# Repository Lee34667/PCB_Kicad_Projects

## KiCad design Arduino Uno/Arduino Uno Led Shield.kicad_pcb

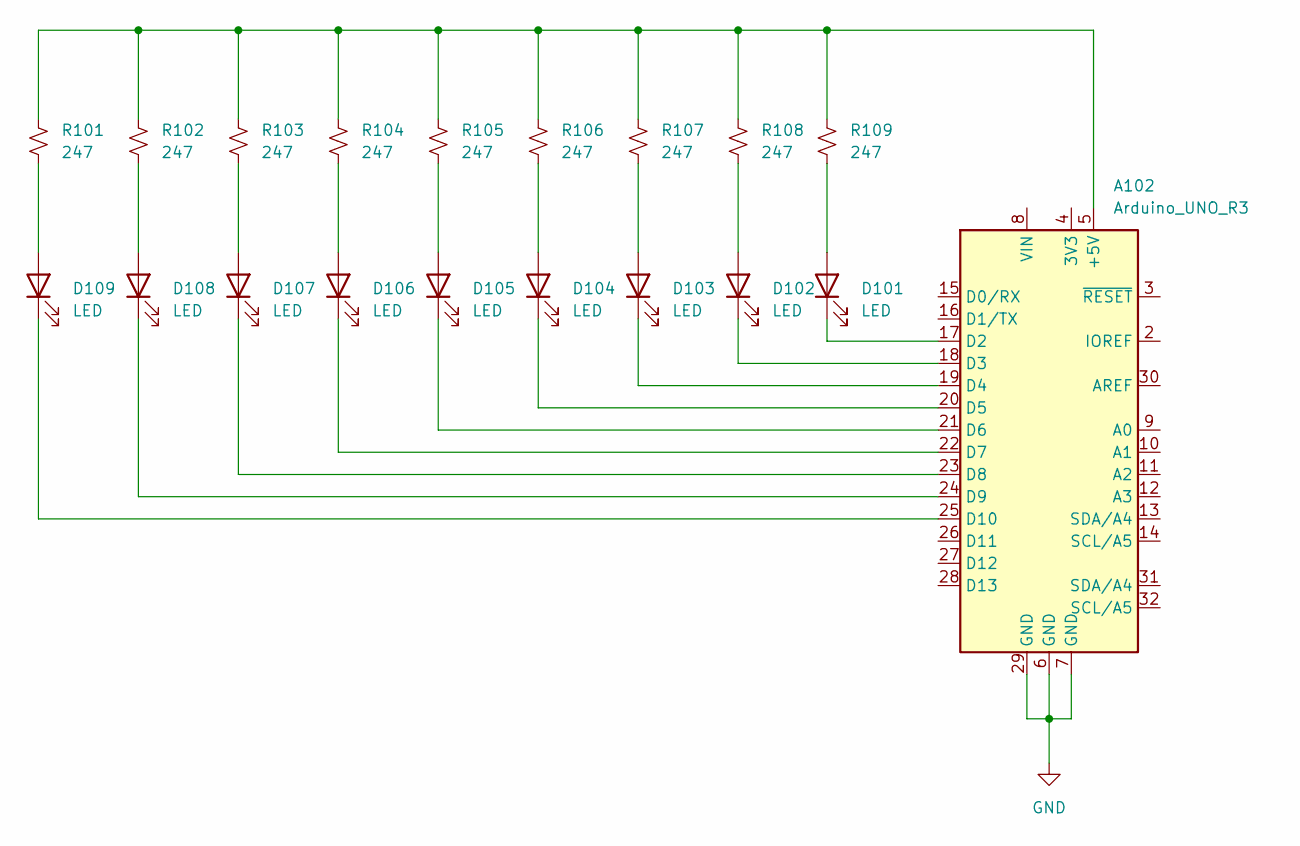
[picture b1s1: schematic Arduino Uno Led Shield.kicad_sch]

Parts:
A102: Arduino_UNO_R3
D101, D102, D103, D104, D105, D106, D107, D108, D109: LED; LED_0805_2012Metric
R101, R102, R103, R104, R105, R106, R107, R108, R109: 247; R_0603_1608Metric

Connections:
unnamed 1: A102.5 (+5V), R101.1, R102.1, R103.1, R104.1, R105.1, R106.1, R107.1, R108.1, R109.1; also elsewhere on the board
unnamed 2: A102.17 (D2), D101.1 (K); also elsewhere on the board
unnamed 3: A102.18 (D3), D102.1 (K); also elsewhere on the board
unnamed 4: A102.19 (D4), D103.1 (K); also elsewhere on the board
unnamed 5: A102.20 (D5), D104.1 (K); also elsewhere on the board
unnamed 6: A102.21 (D6), D105.1 (K); also elsewhere on the board
unnamed 7: A102.22 (D7), D106.1 (K); also elsewhere on the board
unnamed 8: A102.23 (D8), D107.1 (K); also elsewhere on the board
unnamed 9: A102.24 (D9), D108.1 (K); also elsewhere on the board
unnamed 10: A102.25 (D10), D109.1 (K); also elsewhere on the board
unnamed: A102.6 (GND), A102.7 (GND), A102.29 (GND)
unnamed: D101.2 (A), R109.2
unnamed: D102.2 (A), R108.2
unnamed: D103.2 (A), R107.2
unnamed: D104.2 (A), R106.2
unnamed: D105.2 (A), R105.2
unnamed: D106.2 (A), R104.2
unnamed: D107.2 (A), R103.2
unnamed: D108.2 (A), R102.2
unnamed: D109.2 (A), R101.2

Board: 2 copper layers, 19 parts (0 on the bottom side), 20 nets, no tracks yet.

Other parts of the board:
A101: Arduino_UNO_R2

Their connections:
GND: A101.6 (GND), A101.7 (GND), A101.29 (GND)
unnamed 1: A101.5 (+5V); also elsewhere on the board
unnamed 2: A101.17 (D2); also elsewhere on the board
unnamed 3: A101.18 (D3); also elsewhere on the board
unnamed 4: A101.19 (D4); also elsewhere on the board
unnamed 5: A101.20 (D5); also elsewhere on the board
unnamed 6: A101.21 (D6); also elsewhere on the board
unnamed 7: A101.22 (D7); also elsewhere on the board
unnamed 8: A101.23 (D8); also elsewhere on the board
unnamed 9: A101.24 (D9); also elsewhere on the board
unnamed 10: A101.25 (D10); also elsewhere on the board

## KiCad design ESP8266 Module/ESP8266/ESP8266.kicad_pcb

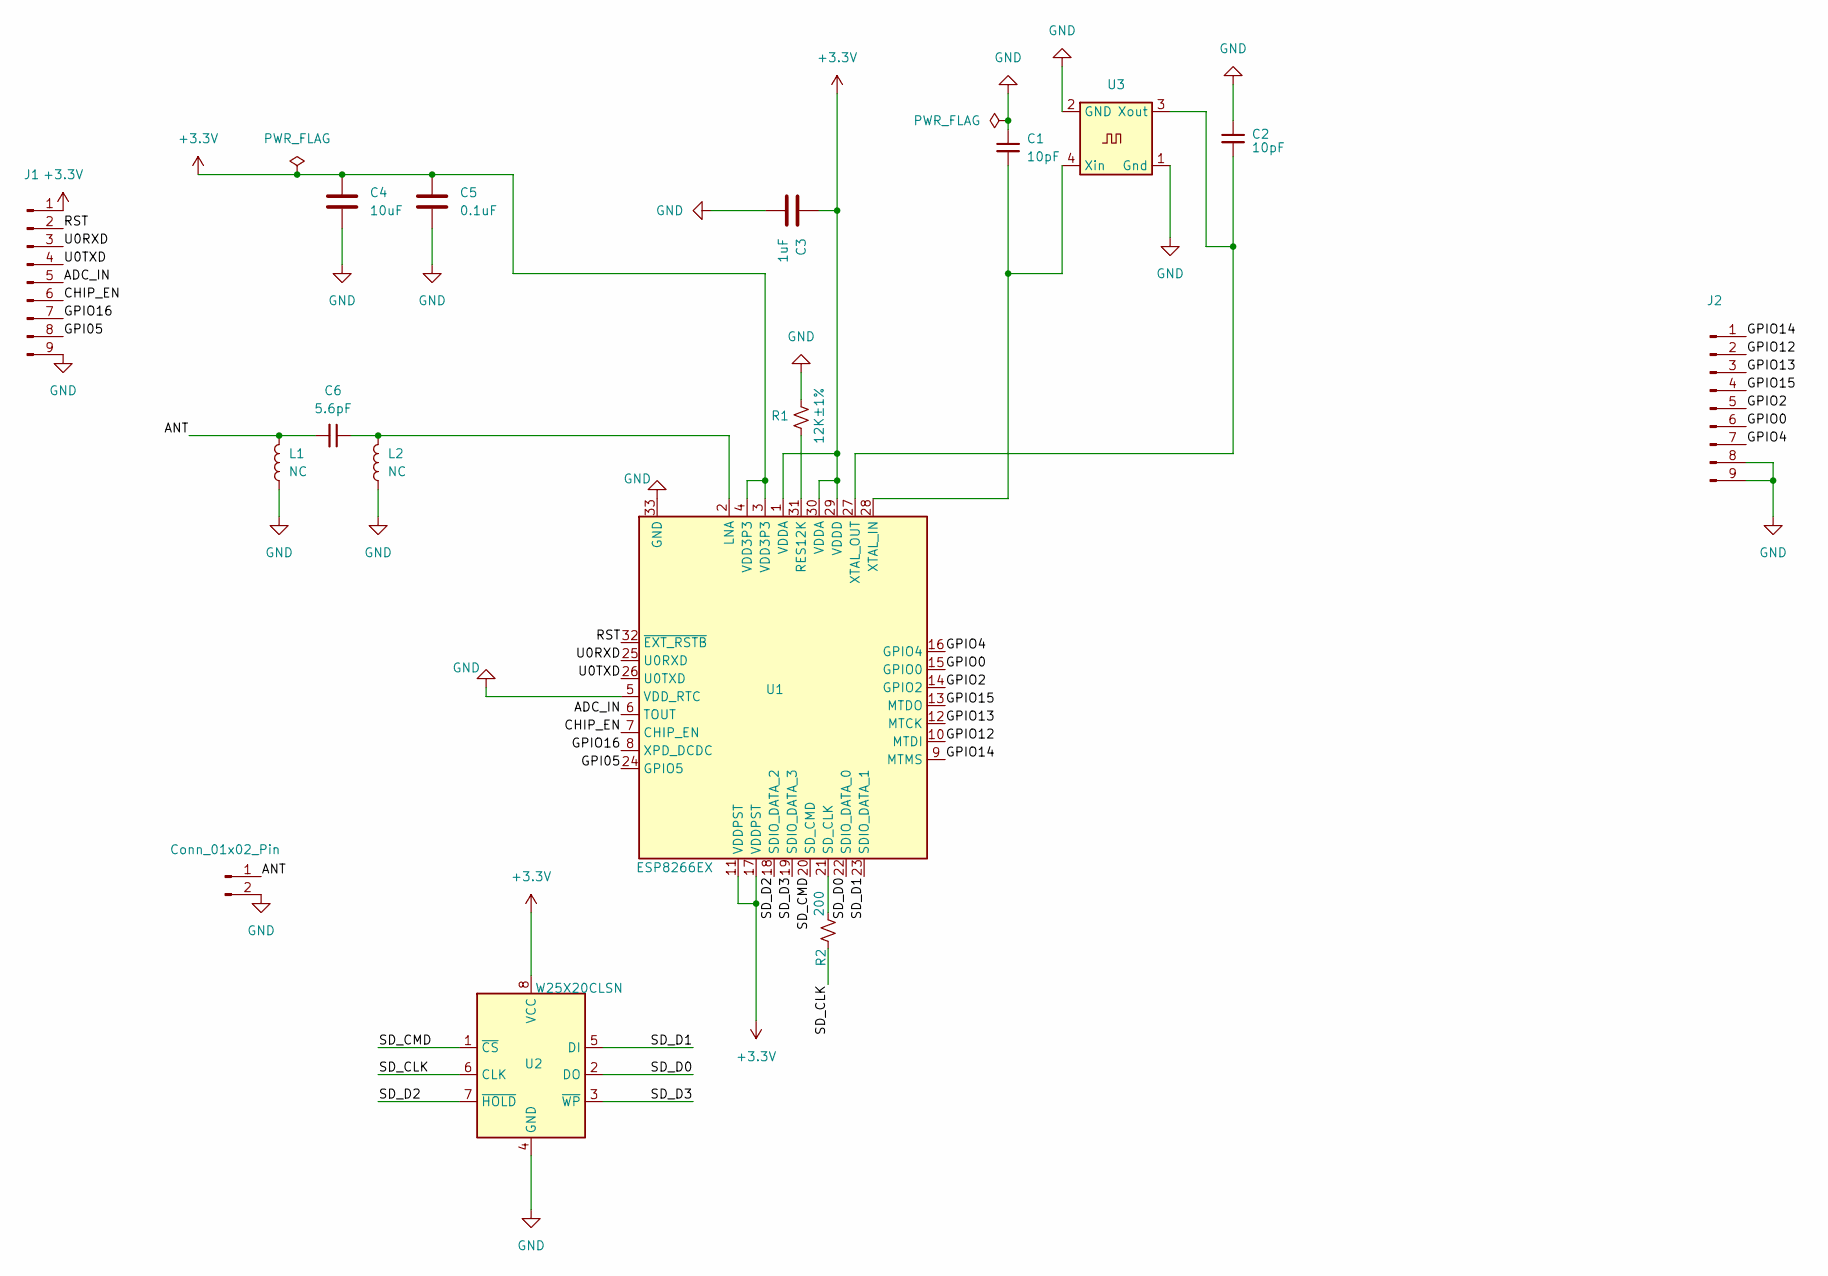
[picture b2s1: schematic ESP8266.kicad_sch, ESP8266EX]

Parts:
C1, C2: 10pF; C_0603_1608Metric_Pad1.08x0.95mm_HandSolder
C3: 1uF; C_0603_1608Metric_Pad1.08x0.95mm_HandSolder
C4: 10uF; C_0603_1608Metric_Pad1.08x0.95mm_HandSolder
C5: 0.1uF; C_0603_1608Metric_Pad1.08x0.95mm_HandSolder
C6: 5.6pF; C_0603_1608Metric_Pad1.08x0.95mm_HandSolder
J1: Conn_01x09_Pin; PinHeader_1x09_P2.54mm_Vertical
J2: PinHeader_1x09_P2.54mm_Vertical
J3: Conn_01x02_Pin; PinHeader_1x02_P2.54mm_Horizontal
L1, L2: NC; L_1206_3216Metric_Pad1.22x1.90mm_HandSolder
R1: 12K±1%; R_0805_2012Metric_Pad1.20x1.40mm_HandSolder
R2: 200; R_0805_2012Metric_Pad1.20x1.40mm_HandSolder
U1: ESP8266EX; QFN-32-1EP_5x5mm_P0.5mm_EP3.45x3.45mm
U2: W25X20CLSN; SOIC-8_3.9x4.9mm_P1.27mm
X1: U3; Oscillator_SMD_SeikoEpson_SG3030CM

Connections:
+3.3V: C3.1, C4.1, C5.1, J1.1, U1.1 (VDDA), U1.3 (VDD3P3), U1.4 (VDD3P3), U1.11 (VDDPST), U1.17 (VDDPST), U1.29 (VDDD), U1.30 (VDDA), U2.8 (VCC)
/ADC_IN: J1.5, U1.6 (TOUT)
/ANT: C6.2, J3.1, L1.2
/CHIP_EN: J1.6, U1.7 (CHIP_EN)
/GPI05: J1.8, U1.24 (GPIO5)
/GPIO0: J2.6, U1.15 (GPIO0)
/GPIO2: J2.5, U1.14 (GPIO2)
/GPIO4: J2.7, U1.16 (GPIO4)
/GPIO12: J2.2, U1.10 (MTDI)
/GPIO13: J2.3, U1.12 (MTCK)
/GPIO14: J2.1, U1.9 (MTMS)
/GPIO15: J2.4, U1.13 (MTDO)
/GPIO16: J1.7, U1.8 (XPD_DCDC)
/RST: J1.2, U1.32 (~EXT_RSTB)
/SD_CLK: R2.1, U2.6 (CLK)
/SD_CMD: U1.20 (SD_CMD), U2.1 (~CS)
/SD_D0: U1.22 (SDIO_DATA_0), U2.2 (DO)
/SD_D1: U1.23 (SDIO_DATA_1), U2.5 (DI)
/SD_D2: U1.18 (SDIO_DATA_2), U2.7 (~HOLD)
/SD_D3: U1.19 (SDIO_DATA_3), U2.3 (~WP)
/U0RXD: J1.3, U1.25 (U0RXD)
/U0TXD: J1.4, U1.26 (U0TXD)
GND: C1.1, C2.1, C3.2, C4.2, C5.2, J1.9, J2.8, J2.9, J3.2, L1.1, L2.1, R1.1, U1.5 (VDD_RTC), U1.33 (GND), U2.4 (GND), X1.1 (Gnd), X1.2 (GND)
unnamed: C6.1, L2.2, U1.2 (LNA)
unnamed: R1.2, U1.31 (RES12K)
unnamed: R2.2, U1.21 (SD_CLK)
unnamed: C1.2, U1.28 (XTAL_IN), X1.4 (Xin)
unnamed: C2.2, U1.27 (XTAL_OUT), X1.3 (Xout)

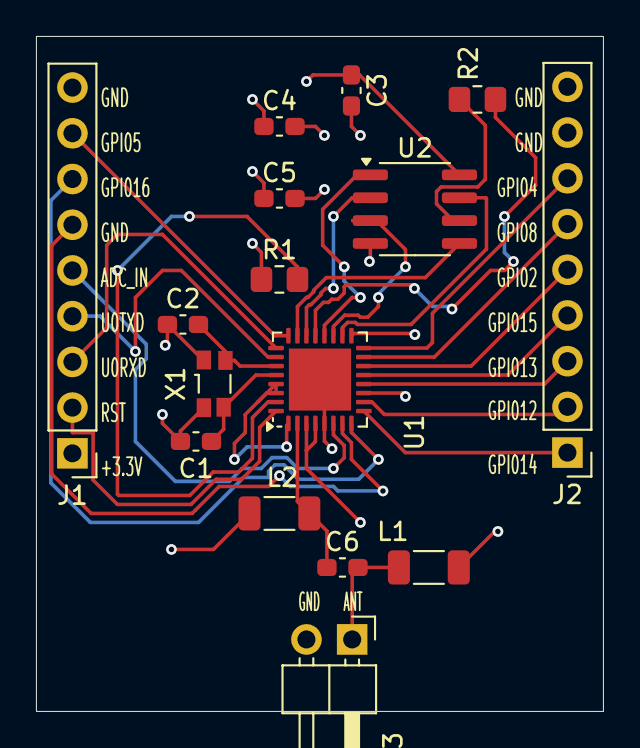
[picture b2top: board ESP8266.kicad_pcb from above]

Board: 4 copper layers, 31.5 x 37.5 mm, 16 parts (0 on the bottom side), 28 nets.

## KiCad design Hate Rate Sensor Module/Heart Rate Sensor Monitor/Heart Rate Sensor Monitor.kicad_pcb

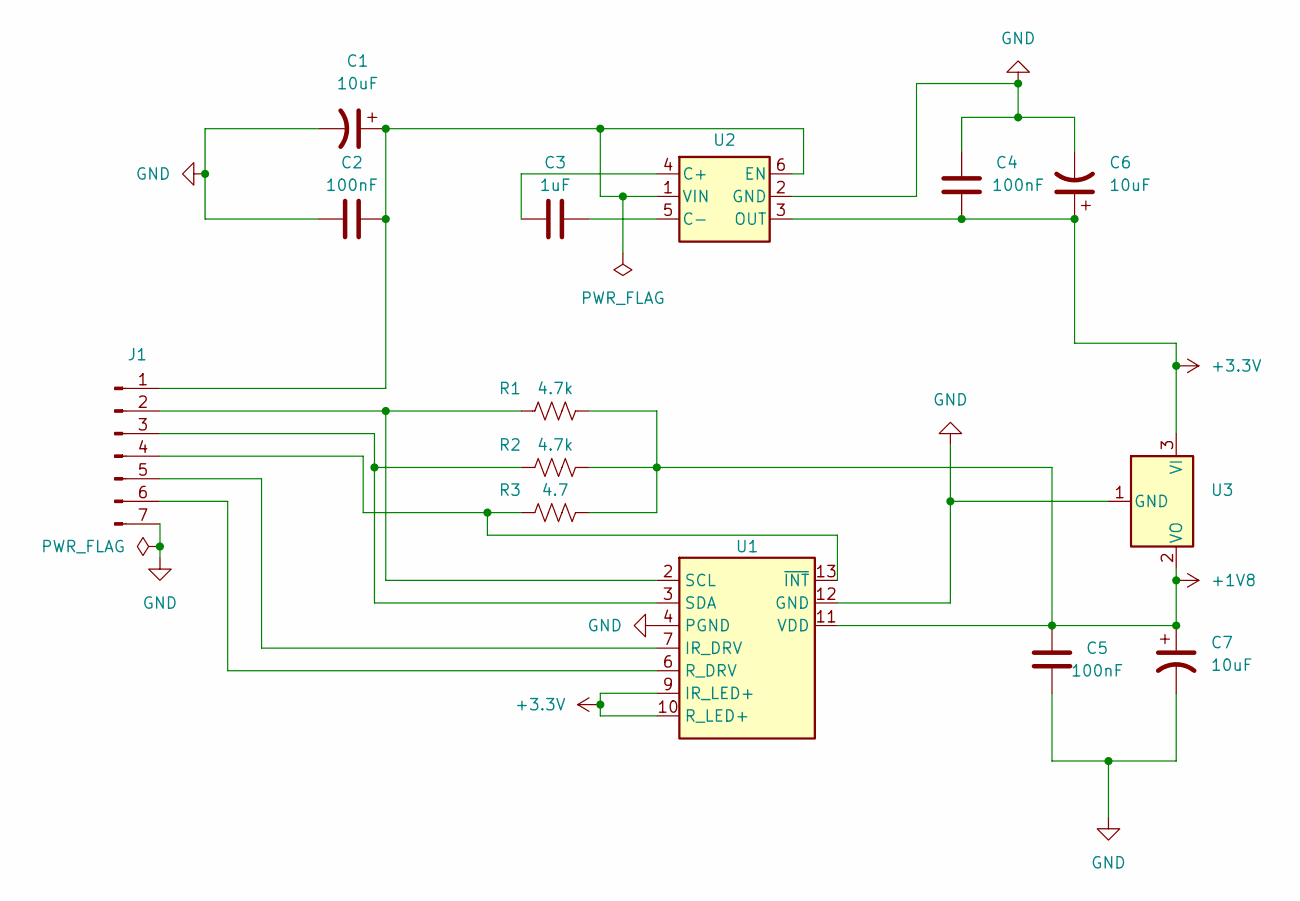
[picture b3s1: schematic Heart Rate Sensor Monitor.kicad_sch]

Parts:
C1, C6, C7: 10uF; C_0504_1310Metric_Pad0.83x1.28mm_HandSolder
C2, C4, C5: 100nF; C_0504_1310Metric_Pad0.83x1.28mm_HandSolder
C3: 1uF; C_0504_1310Metric_Pad0.83x1.28mm_HandSolder
J1: Conn_01x07_Pin; PinHeader_1x07_P1.27mm_Vertical
R1, R2: 4.7k; R_0603_1608Metric_Pad0.98x0.95mm_HandSolder
R3: 4.7; R_0603_1608Metric_Pad0.98x0.95mm_HandSolder
U1: MAX30102; Maxim_OLGA-14_3.3x5.6mm_P0.8mm
U2: TLV70028_WSON6; WSON-6_1.5x1.5mm_P0.5mm
U3: TPS7A0512PDBZ; SOT-23

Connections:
+1V8: C5.2, C7.1, R1.2, R2.2, R3.2, U1.11 (VDD), U3.2 (VO)
+3.3V: C4.1, C6.1, U1.9 (IR_LED+), U1.10 (R_LED+), U2.3 (OUT), U3.3 (VI)
GND: C1.2, C2.1, C4.2, C5.1, C6.2, C7.2, J1.7, U1.4 (PGND), U1.12 (GND), U2.2 (GND), U3.1 (GND)
unnamed: C1.1, C2.2, J1.1, U2.1 (VIN), U2.6 (EN)
unnamed: J1.2, R1.1, U1.2 (SCL)
unnamed: J1.3, R2.1, U1.3 (SDA)
unnamed: J1.4, R3.1, U1.13 (~INT)
unnamed: J1.5, U1.7 (IR_DRV)
unnamed: J1.6, U1.6 (R_DRV)
unnamed: C3.2, U2.4 (C+)
unnamed: C3.1, U2.5 (C-)

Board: 2 copper layers, 14 parts (0 on the bottom side), 11 nets, no tracks yet.

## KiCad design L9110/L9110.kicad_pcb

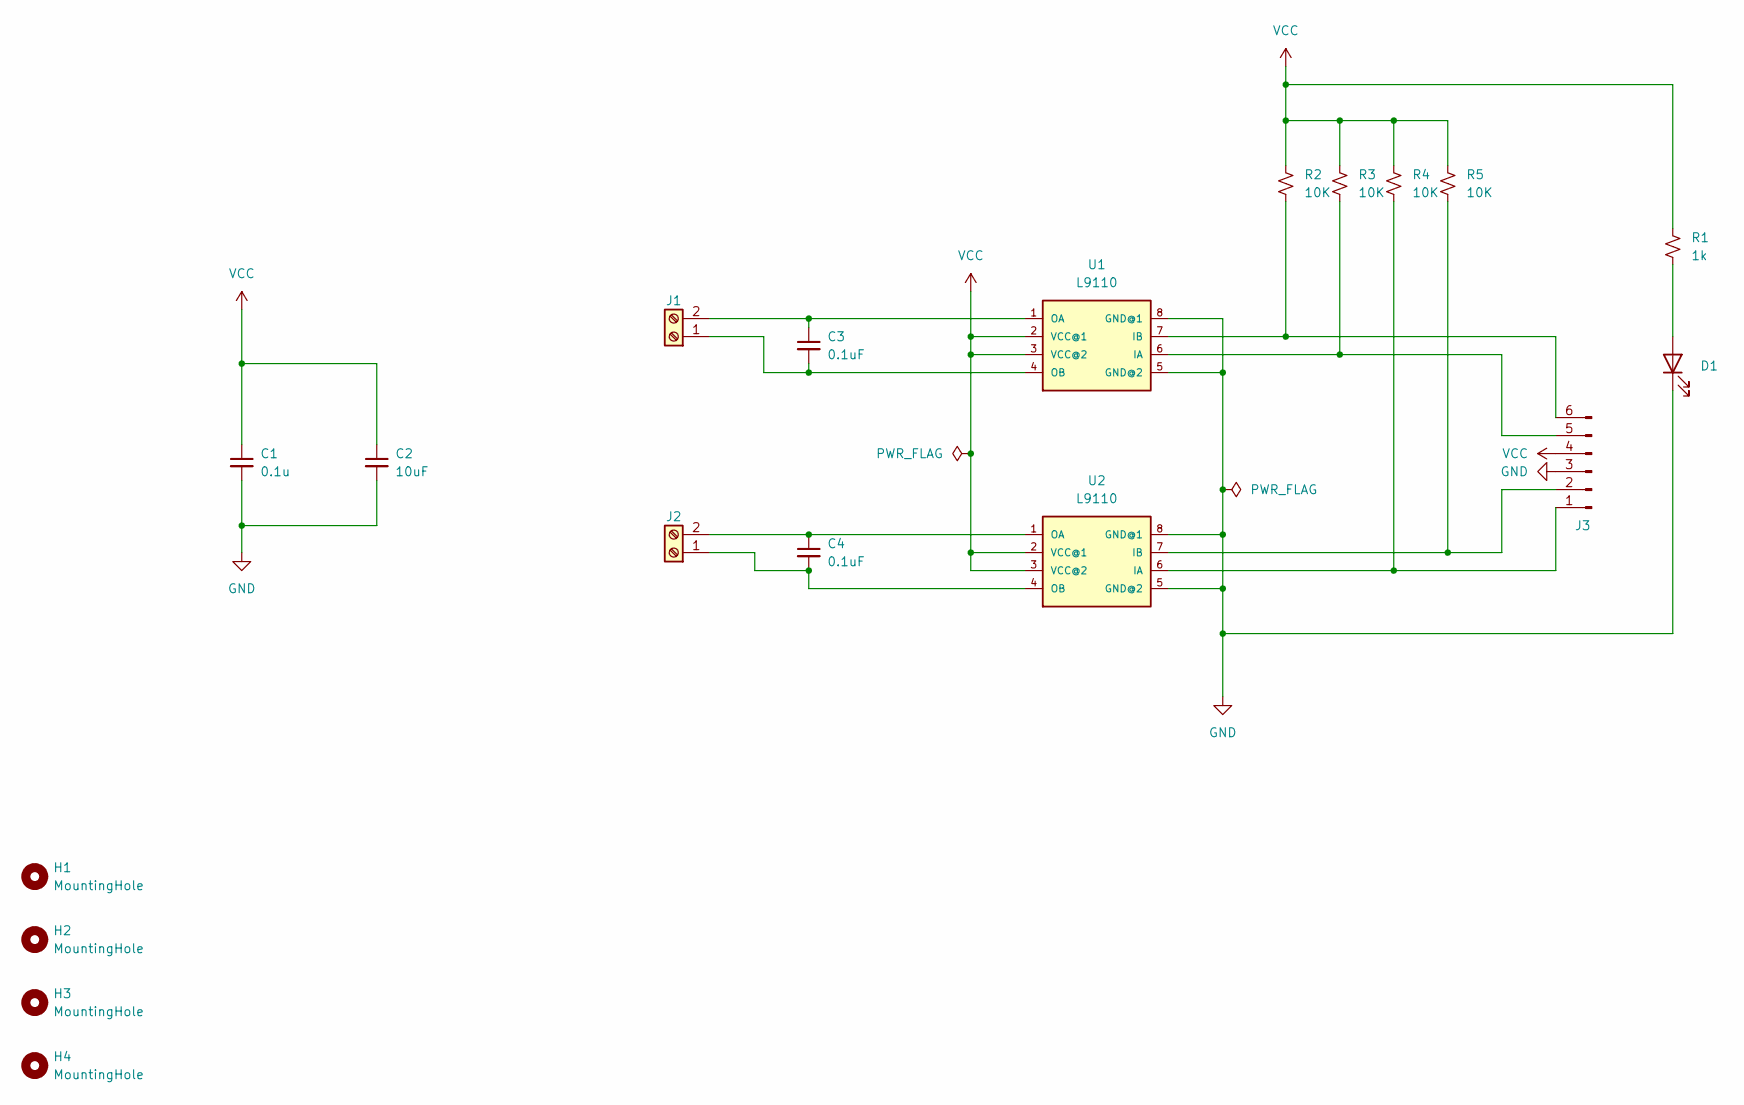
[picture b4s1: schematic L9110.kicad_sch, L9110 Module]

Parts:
C1: 0.1u; C_0201_0603Metric
C2: 10uF; C_0201_0603Metric
C3, C4: 0.1uF; C_0201_0603Metric
D1: LED; LED_0201_0603Metric
H1, H2, H3, H4: MountingHole; MountingHole_2.1mm
J1, J2: Screw_Terminal_01x02; TerminalBlock_Phoenix_MKDS-1,5-2_1x02_P5.00mm_Horizontal
J3: Conn_01x06_Pin; PinHeader_1x06_P2.54mm_Vertical
R1: 1k; R_0201_0603Metric
R2, R3, R4, R5: 10K; R_0201_0603Metric
U1, U2: L9110; SO-08

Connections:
GND: C1.2, C2.2, D1.1 (K), J3.3, U1.5 (GND@2), U1.8 (GND@1), U2.5 (GND@2), U2.8 (GND@1)
unnamed: D1.2 (A), R1.2
unnamed: C3.2, J1.1, U1.4 (OB)
unnamed: C3.1, J1.2, U1.1 (OA)
unnamed: C4.2, J2.1, U2.4 (OB)
unnamed: C4.1, J2.2, U2.1 (OA)
unnamed: J3.1, R4.2, U2.6 (IA)
unnamed: J3.2, R5.2, U2.7 (IB)
unnamed: J3.5, R3.2, U1.6 (IA)
unnamed: J3.6, R2.2, U1.7 (IB)
VCC: C1.1, C2.1, J3.4, R1.1, R2.1, R3.1, R4.1, R5.1, U1.2 (VCC@1), U1.3 (VCC@2), U2.2 (VCC@1), U2.3 (VCC@2)

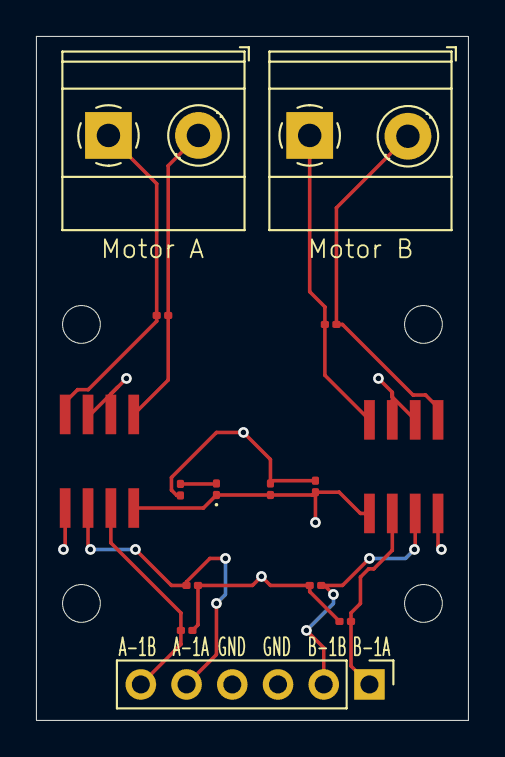
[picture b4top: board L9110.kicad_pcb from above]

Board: 4 copper layers, 24.0 x 38.0 mm, 19 parts (0 on the bottom side), 11 nets.

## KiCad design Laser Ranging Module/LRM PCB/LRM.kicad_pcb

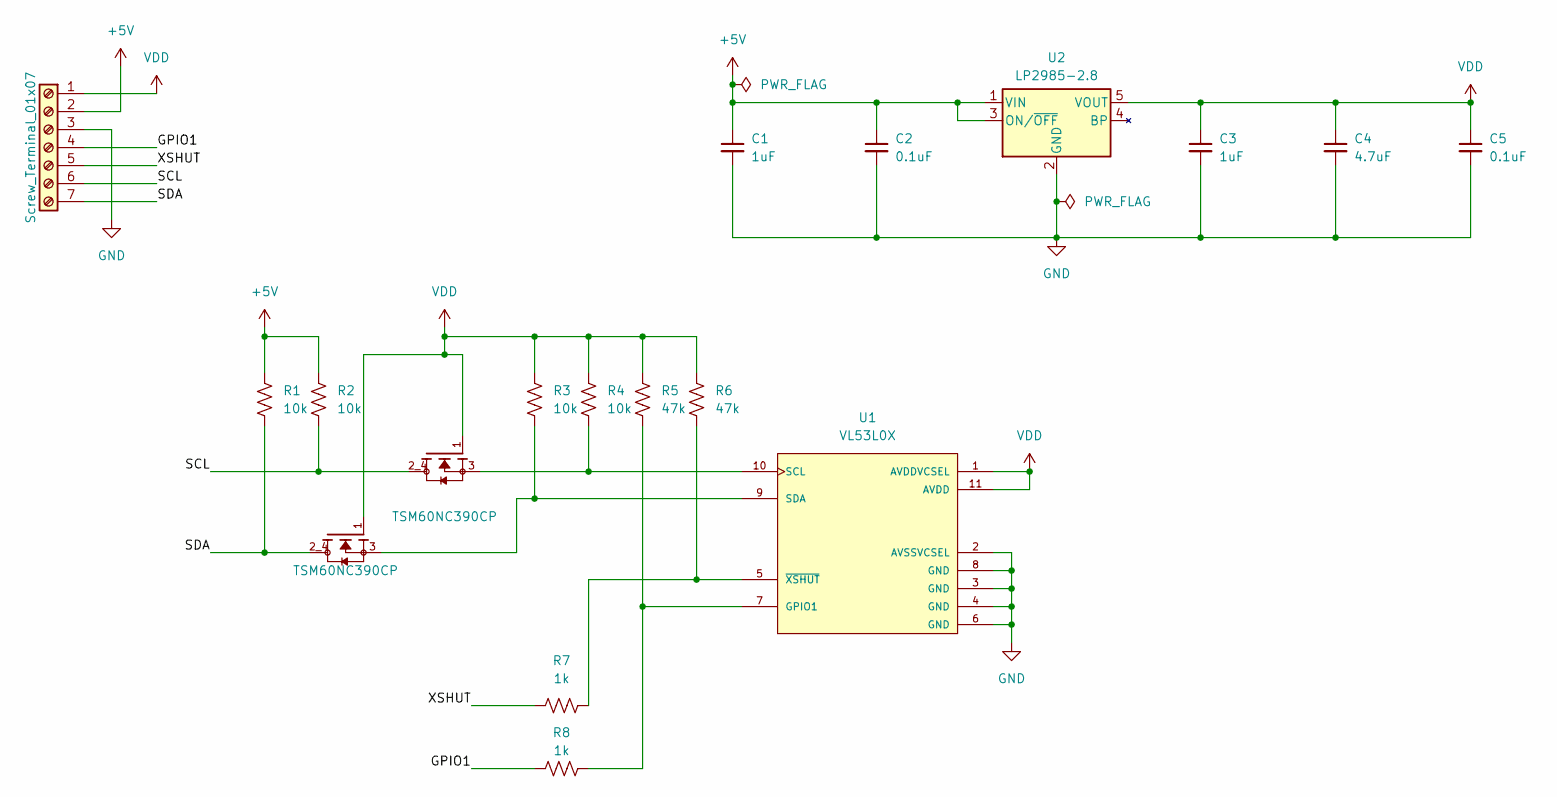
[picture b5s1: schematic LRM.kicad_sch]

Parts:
C1, C3: 1uF; C_1206_3216Metric_Pad1.33x1.80mm_HandSolder
C2, C5: 0.1uF; C_1206_3216Metric_Pad1.33x1.80mm_HandSolder
C4: 4.7uF; C_1206_3216Metric_Pad1.33x1.80mm_HandSolder
J1: Screw_Terminal_01x07; TerminalBlock_Phoenix_MKDS-1,5-7_1x07_P5.00mm_Horizontal
Q1, Q2: TSM60NC390CP; TRANS_TSM60NC390CP; PARTREV C2401
R1, R2, R3, R4: 10k; R_1206_3216Metric_Pad1.30x1.75mm_HandSolder
R5, R6: 47k; R_1206_3216Metric_Pad1.30x1.75mm_HandSolder
R7, R8: 1k; R_1206_3216Metric_Pad1.30x1.75mm_HandSolder
U1: VL53L0X; SENSOR_VL53L0X; PART_REV 1.0
U2: LP2985-2.8; SOT-23-5

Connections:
+5V: C1.1, C2.1, J1.2, R1.1, R2.1, U2.1 (VIN), U2.3 (ON/~OFF)
/GPIO1: J1.4, R8.1
/SCL: J1.6, Q2.2_4, R2.2
/SDA: J1.7, Q1.2_4, R1.2
/XSHUT: J1.5, R7.1
GND: C1.2, C2.2, C3.2, C4.2, C5.2, J1.3, U1.2 (AVSSVCSEL), U1.3 (GND), U1.4 (GND), U1.6 (GND), U1.8 (GND), U2.2 (GND)
unnamed: R5.2, R8.2, U1.7 (GPIO1)
unnamed: Q2.3, R4.2, U1.10 (SCL)
unnamed: Q1.3, R3.2, U1.9 (SDA)
unnamed: R6.2, R7.2, U1.5 (~XSHUT)
VDD: C3.1, C4.1, C5.1, J1.1, Q1.1, Q2.1, R3.1, R4.1, R5.1, R6.1, U1.1 (AVDDVCSEL), U1.11 (AVDD), U2.5 (VOUT)

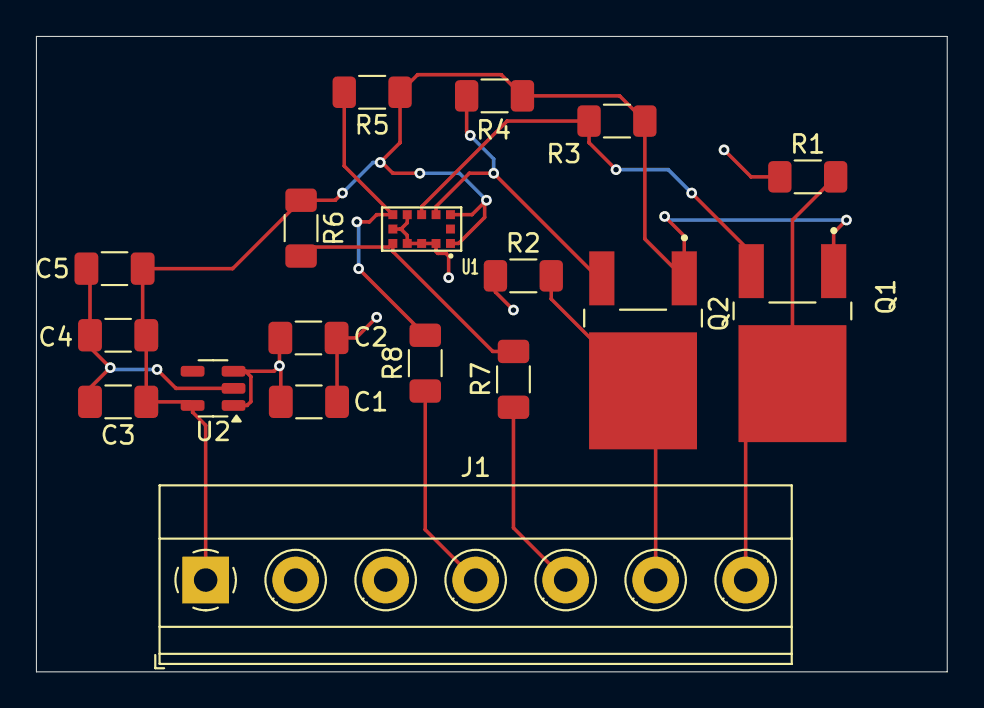
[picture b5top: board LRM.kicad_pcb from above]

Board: 4 copper layers, 50.6 x 35.3 mm, 18 parts (0 on the bottom side), 11 nets.

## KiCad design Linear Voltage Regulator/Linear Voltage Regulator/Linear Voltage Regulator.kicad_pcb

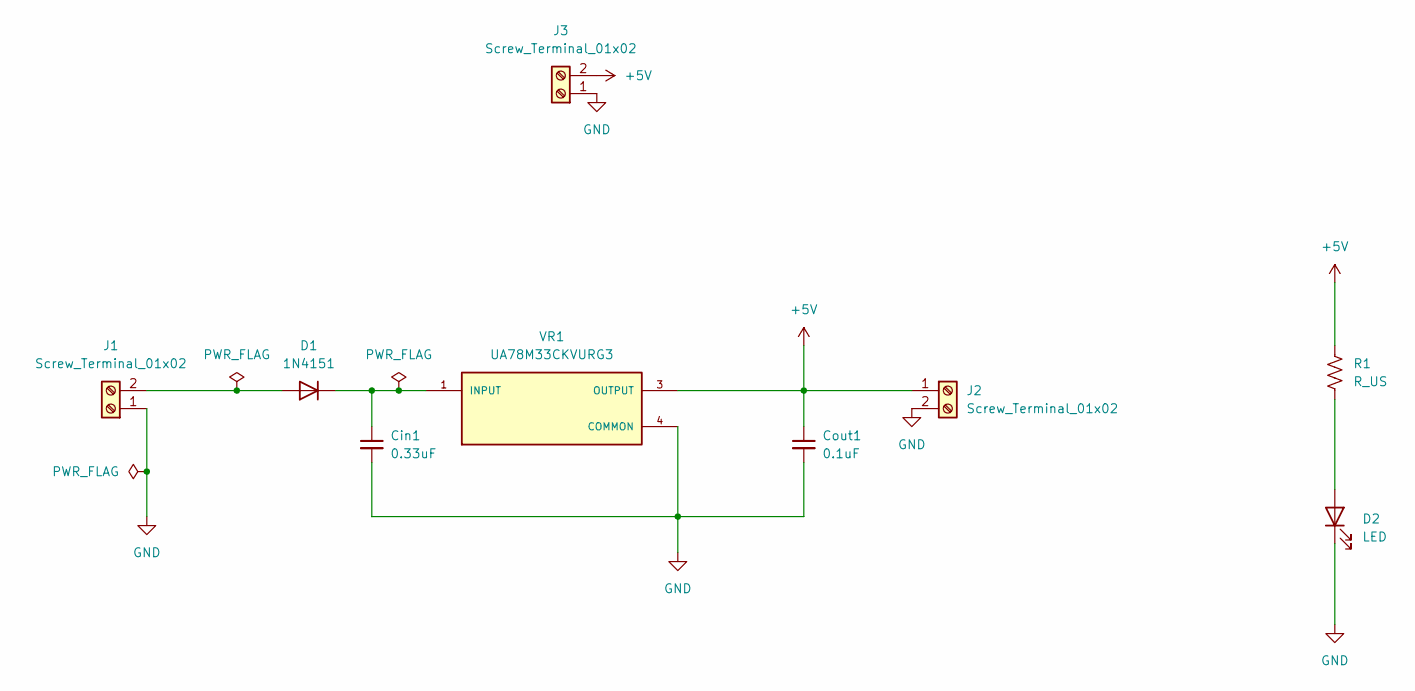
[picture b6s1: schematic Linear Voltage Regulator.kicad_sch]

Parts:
Cin1: 0.33uF; C_0504_1310Metric_Pad0.83x1.28mm_HandSolder
Cout1: 0.1uF; C_0504_1310Metric_Pad0.83x1.28mm_HandSolder
D1: 1N4151; D_DO-35_SOD27_P7.62mm_Horizontal
D2: LED; LED_0603_1608Metric_Pad1.05x0.95mm_HandSolder
J1, J2, J3: Screw_Terminal_01x02; TerminalBlock_Phoenix_MKDS-1,5-2-5.08_1x02_P5.08mm_Horizont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
R1: R_US; R_1020_2550Metric_Pad1.33x5.20mm_HandSolder
VR1: UA78M33CKVURG3; TO229P990X252-3N; PARTREV T

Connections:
+5V: Cout1.1, J2.1, J3.2, R1.1, VR1.3 (OUTPUT)
GND: Cin1.2, Cout1.2, D2.1 (K), J1.1, J2.2, J3.1, VR1.4 (COMMON)
unnamed: D1.2 (A), J1.2
unnamed: Cin1.1, D1.1 (K), VR1.1 (INPUT)
unnamed: D2.2 (A), R1.2

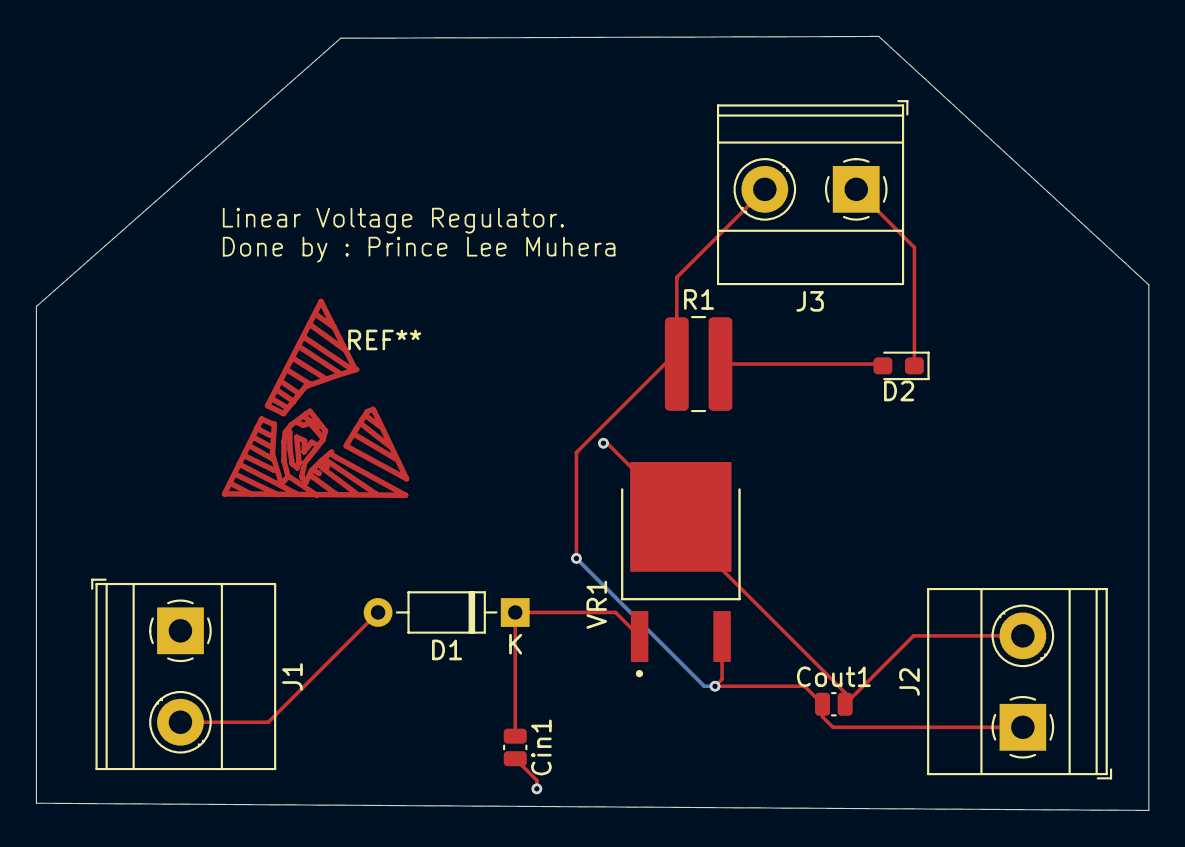
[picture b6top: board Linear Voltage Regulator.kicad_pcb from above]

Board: 2 copper layers, 61.8 x 43.0 mm, 9 parts (0 on the bottom side), 5 nets.

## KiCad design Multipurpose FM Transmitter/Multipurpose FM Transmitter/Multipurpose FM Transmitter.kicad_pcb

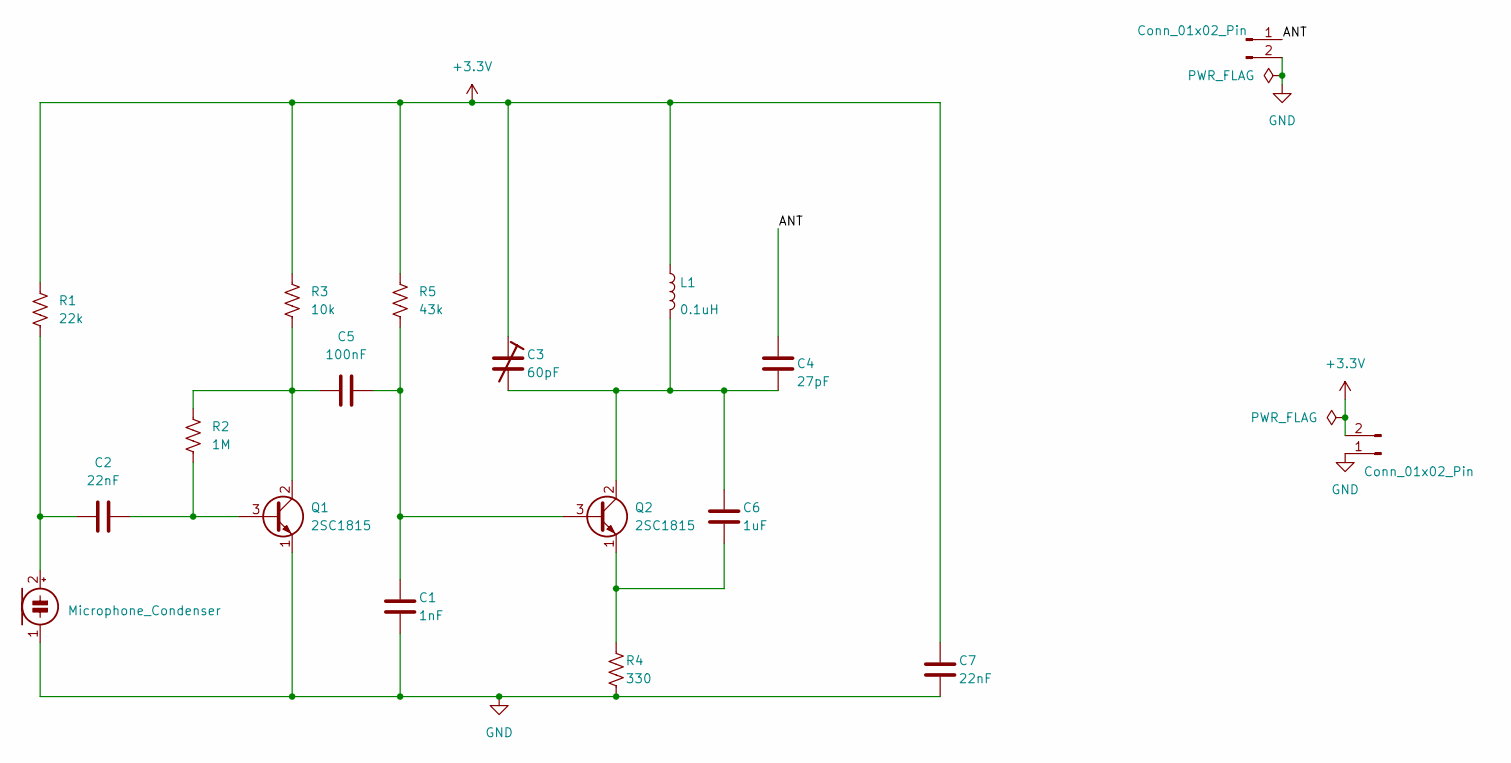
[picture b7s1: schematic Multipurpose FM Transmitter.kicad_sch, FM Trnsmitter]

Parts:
C1: 1nF; C_1812_4532Metric_Pad1.57x3.40mm_HandSolder
C2, C7: 22nF; C_1812_4532Metric_Pad1.57x3.40mm_HandSolder
C3: 60pF; C_1812_4532Metric_Pad1.57x3.40mm_HandSolder
C4: 27pF; C_1812_4532Metric_Pad1.57x3.40mm_HandSolder
C5: 100nF; C_1812_4532Metric_Pad1.57x3.40mm_HandSolder
C6: 1uF; C_1812_4532Metric_Pad1.57x3.40mm_HandSolder
J1, J2: Conn_01x02_Pin; PinHeader_1x02_P2.54mm_Vertical
L1: 0.1uH; L_2010_5025Metric_Pad1.52x2.65mm_HandSolder
MK1: Microphone_Condenser; POM-2244P-C3310-2-R
Q1, Q2: 2SC1815; TO-92_Inline
R1: 22k; R_2512_6332Metric_Pad1.40x3.35mm_HandSolder
R2: 1M; R_2512_6332Metric_Pad1.40x3.35mm_HandSolder
R3: 10k; R_2512_6332Metric_Pad1.40x3.35mm_HandSolder
R4: 330; R_2512_6332Metric_Pad1.40x3.35mm_HandSolder
R5: 43k; R_2512_6332Metric_Pad1.40x3.35mm_HandSolder

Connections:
+3.3V: C3.1, C7.1, J1.2, L1.1, R1.1, R3.1, R5.1
/ANT: C4.1, J2.1
GND: C1.1, C7.2, J1.1, J2.2, MK1.1 (-), Q1.1 (E), R4.2
unnamed: C2.2, MK1.2 (+), R1.2
unnamed: C2.1, Q1.3 (B), R2.2
unnamed: C5.1, Q1.2 (C), R2.1, R3.2
unnamed: C1.2, C5.2, Q2.3 (B), R5.2
unnamed: C3.2, C4.2, C6.1, L1.2, Q2.2 (C)
unnamed: C6.2, Q2.1 (E), R4.1

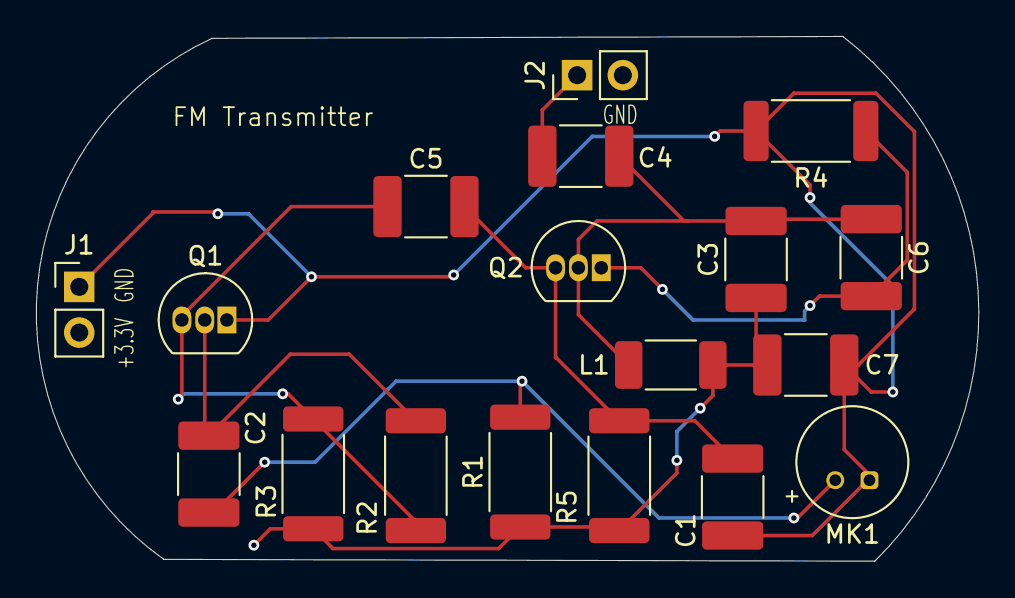
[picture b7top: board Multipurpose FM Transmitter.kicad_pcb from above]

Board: 4 copper layers, 52.4 x 29.2 mm, 18 parts (0 on the bottom side), 9 nets.
